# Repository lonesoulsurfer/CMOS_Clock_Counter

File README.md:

# CMOS Clock Counter
 A clock made from CMOS IC's that counts in second increments

This little clock counts the seconds up to 99,999 (1.15 Days) and then starts over again. I wanted it to be a visual reminder of the seconds ticking by and to try and not waste to many of them.

The clock is really a count up counter.  It uses the 4060 Binary counter CMOS chip to keep accurate time using a crystal oscillator. The 4060 IC can be used to generate a pulse at 1 second intervals which in turn can be used as a clock input to drive some 4033 Decade Counter CMOS chips to control some 7 segment displays.

The great thing about the 4033 IC is you can string them together in as many rows as you wanted to, meaning you could build a googol clock (1 followed by 100 zeros!) if you felt like it! Most of it would be blank until the end of the universe but it would still be pretty cool thing to build.

I designed a PCB to keep everything neat and tidy and also added some red transparent acrylic across the front to help diffuse the light from the 7 segment displays.

There are 2 versions available, one that runs off a 9V battery (untested) and one that runs off 5V USB C power - Both versions are available.

Instructables step by step guide: https://www.instructables.com/CMOS-Counter-Clock/

Youtube Vid Build: https://www.youtube.com/watch?v=ALrcwJxQYL8&source_ve_path=Mjg2NjY

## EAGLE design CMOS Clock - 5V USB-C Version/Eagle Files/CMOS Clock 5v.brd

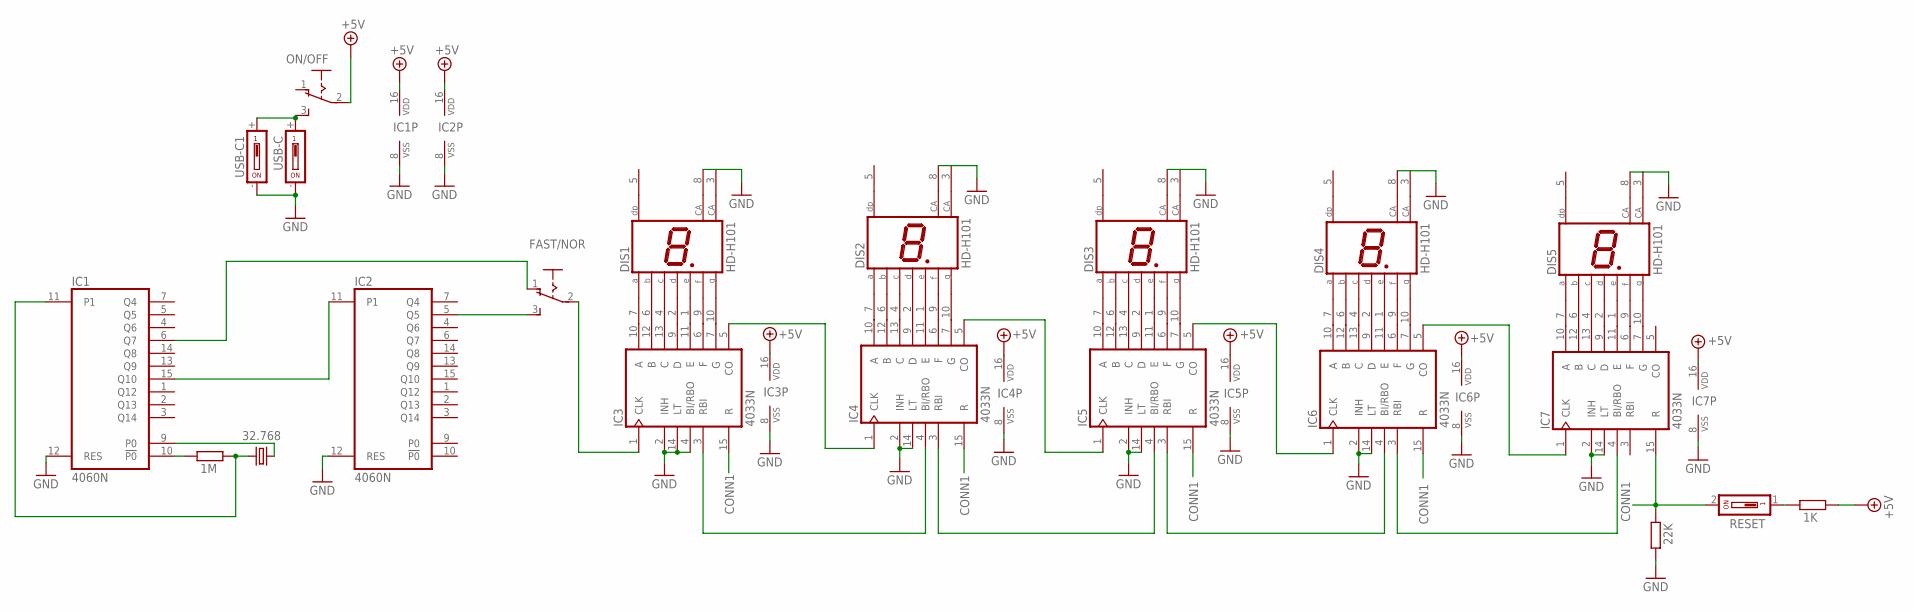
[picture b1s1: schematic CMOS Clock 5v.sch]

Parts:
DIS1, DIS2, DIS3, DIS4, DIS5: HD-H101; HDSP-M
FAST/NOR: M251
IC1, IC2: 4060N; DIL16
IC3, IC4, IC5, IC6, IC7: 4033N; DIL16
ON/OFF: M251
Q1: 32.768; TC26H
R1: 1M; 0207/10
R2: 1K; 0207/10
R3: 22K; 0207/10
RESET: DS01; DS-01
USB-C, USB-C1: USB-C; DS-01

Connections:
+5V: IC1.16 (VDD), IC2.16 (VDD), IC3.16 (VDD), IC4.16 (VDD), IC5.16 (VDD), IC6.16 (VDD), IC7.16 (VDD), ON/OFF.2, R2.2
CONN1: IC3.15 (R), IC4.15 (R), IC5.15 (R), IC6.15 (R), IC7.15 (R), R3.2, RESET.2
GND: DIS1.3 (CA), DIS1.8 (CA), DIS2.3 (CA), DIS2.8 (CA), DIS3.3 (CA), DIS3.8 (CA), DIS4.3 (CA), DIS4.8 (CA), DIS5.3 (CA), DIS5.8 (CA), IC1.8 (VSS), IC1.12 (RES), IC2.8 (VSS), IC2.12 (RES), IC3.2 (INH), IC3.4 (BI/RBO), IC3.8 (VSS), IC3.14 (LT), IC4.2 (INH), IC4.8 (VSS), IC4.14 (LT), IC5.2 (INH), IC5.8 (VSS), IC5.14 (LT), IC6.2 (INH), IC6.8 (VSS), IC6.14 (LT), IC7.2 (INH), IC7.8 (VSS), IC7.14 (LT), R3.1, USB-C.- (2), USB-C1.- (2)
unnamed: IC1.10 (!P0), R1.1
unnamed: IC1.11 (P1), Q1.1, R1.2
unnamed: IC1.9 (P0), Q1.2
unnamed: IC1.15 (Q10), IC2.11 (P1)
unnamed: FAST/NOR.3 (S), IC2.5 (Q5)
unnamed: DIS1.9 (F), IC3.6 (F)
unnamed: DIS1.10 (G), IC3.7 (G)
unnamed: DIS1.2 (D), IC3.9 (D)
unnamed: DIS1.7 (A), IC3.10 (A)
unnamed: DIS1.1 (E), IC3.11 (E)
unnamed: DIS1.6 (B), IC3.12 (B)
unnamed: DIS1.4 (C), IC3.13 (C)
unnamed: IC3.5 (CO), IC4.1 (CLK)
unnamed: IC4.5 (CO), IC5.1 (CLK)
unnamed: DIS2.9 (F), IC4.6 (F)
unnamed: DIS2.10 (G), IC4.7 (G)
unnamed: DIS2.2 (D), IC4.9 (D)
unnamed: DIS2.7 (A), IC4.10 (A)
unnamed: DIS2.1 (E), IC4.11 (E)
unnamed: DIS2.6 (B), IC4.12 (B)
unnamed: DIS2.4 (C), IC4.13 (C)
unnamed: IC5.5 (CO), IC6.1 (CLK)
unnamed: IC6.5 (CO), IC7.1 (CLK)
unnamed: DIS3.9 (F), IC5.6 (F)
unnamed: DIS3.10 (G), IC5.7 (G)
unnamed: DIS3.2 (D), IC5.9 (D)
unnamed: DIS3.7 (A), IC5.10 (A)
unnamed: DIS3.1 (E), IC5.11 (E)
unnamed: DIS3.6 (B), IC5.12 (B)
unnamed: DIS3.4 (C), IC5.13 (C)
unnamed: IC3.3 (RBI), IC4.4 (BI/RBO)
unnamed: IC4.3 (RBI), IC5.4 (BI/RBO)
unnamed: R2.1, RESET.1
unnamed: DIS4.9 (F), IC6.6 (F)
unnamed: DIS4.10 (G), IC6.7 (G)
unnamed: DIS4.2 (D), IC6.9 (D)
unnamed: ON/OFF.3 (S), USB-C.+ (1), USB-C1.+ (1)
unnamed: DIS4.7 (A), IC6.10 (A)
unnamed: DIS4.1 (E), IC6.11 (E)
unnamed: DIS4.6 (B), IC6.12 (B)
unnamed: DIS4.4 (C), IC6.13 (C)
unnamed: IC5.3 (RBI), IC6.4 (BI/RBO)
unnamed: IC6.3 (RBI), IC7.4 (BI/RBO)
unnamed: DIS5.9 (F), IC7.6 (F)
unnamed: FAST/NOR.2, IC3.1 (CLK)
unnamed: DIS5.10 (G), IC7.7 (G)
unnamed: DIS5.2 (D), IC7.9 (D)
unnamed: DIS5.7 (A), IC7.10 (A)
unnamed: DIS5.1 (E), IC7.11 (E)
unnamed: DIS5.6 (B), IC7.12 (B)
unnamed: DIS5.4 (C), IC7.13 (C)
unnamed: FAST/NOR.1 (O), IC1.6 (Q7)

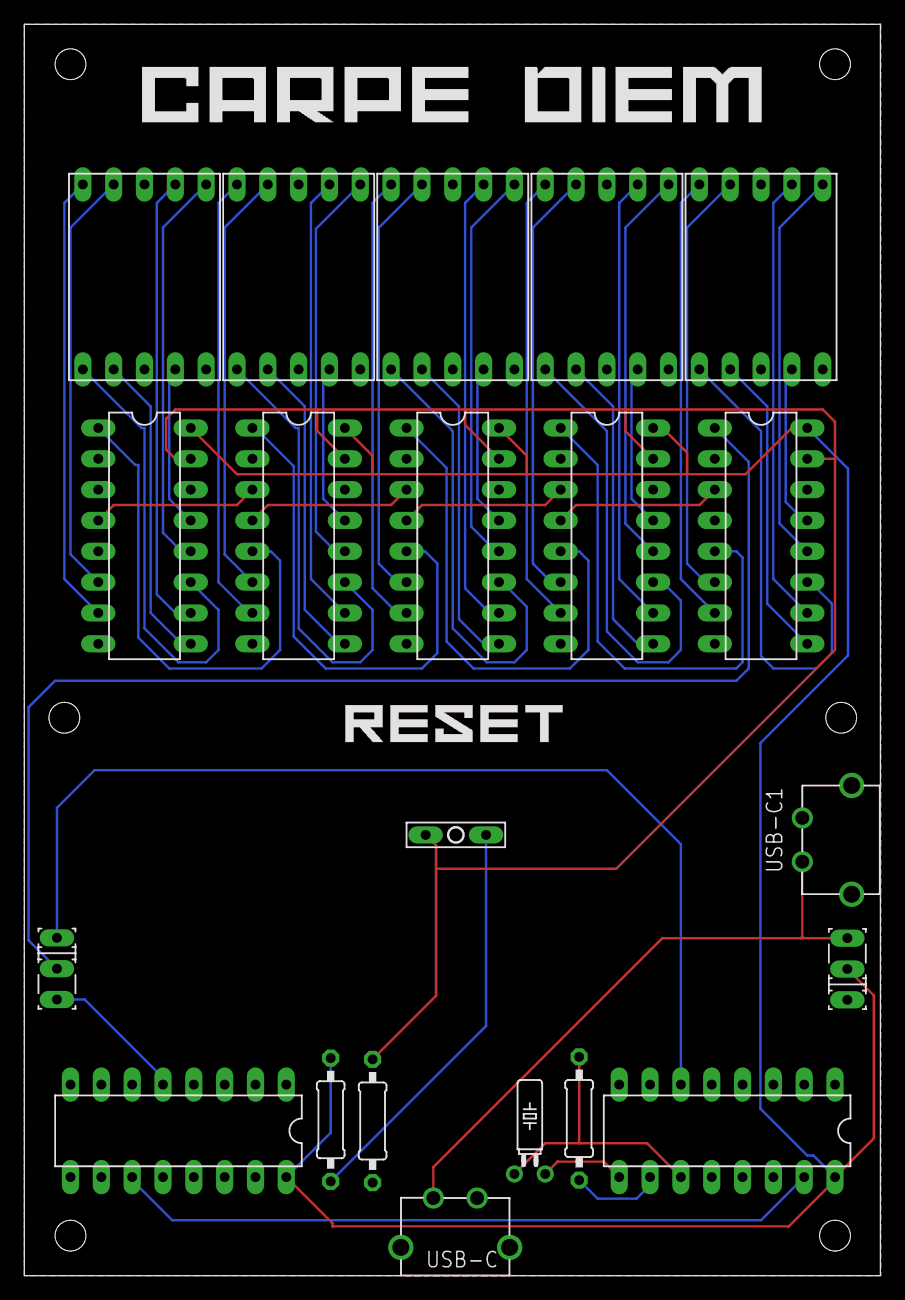
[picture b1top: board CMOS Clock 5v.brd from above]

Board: 2 copper layers, 70.5 x 103.1 mm, 21 parts (0 on the bottom side), 55 nets.
